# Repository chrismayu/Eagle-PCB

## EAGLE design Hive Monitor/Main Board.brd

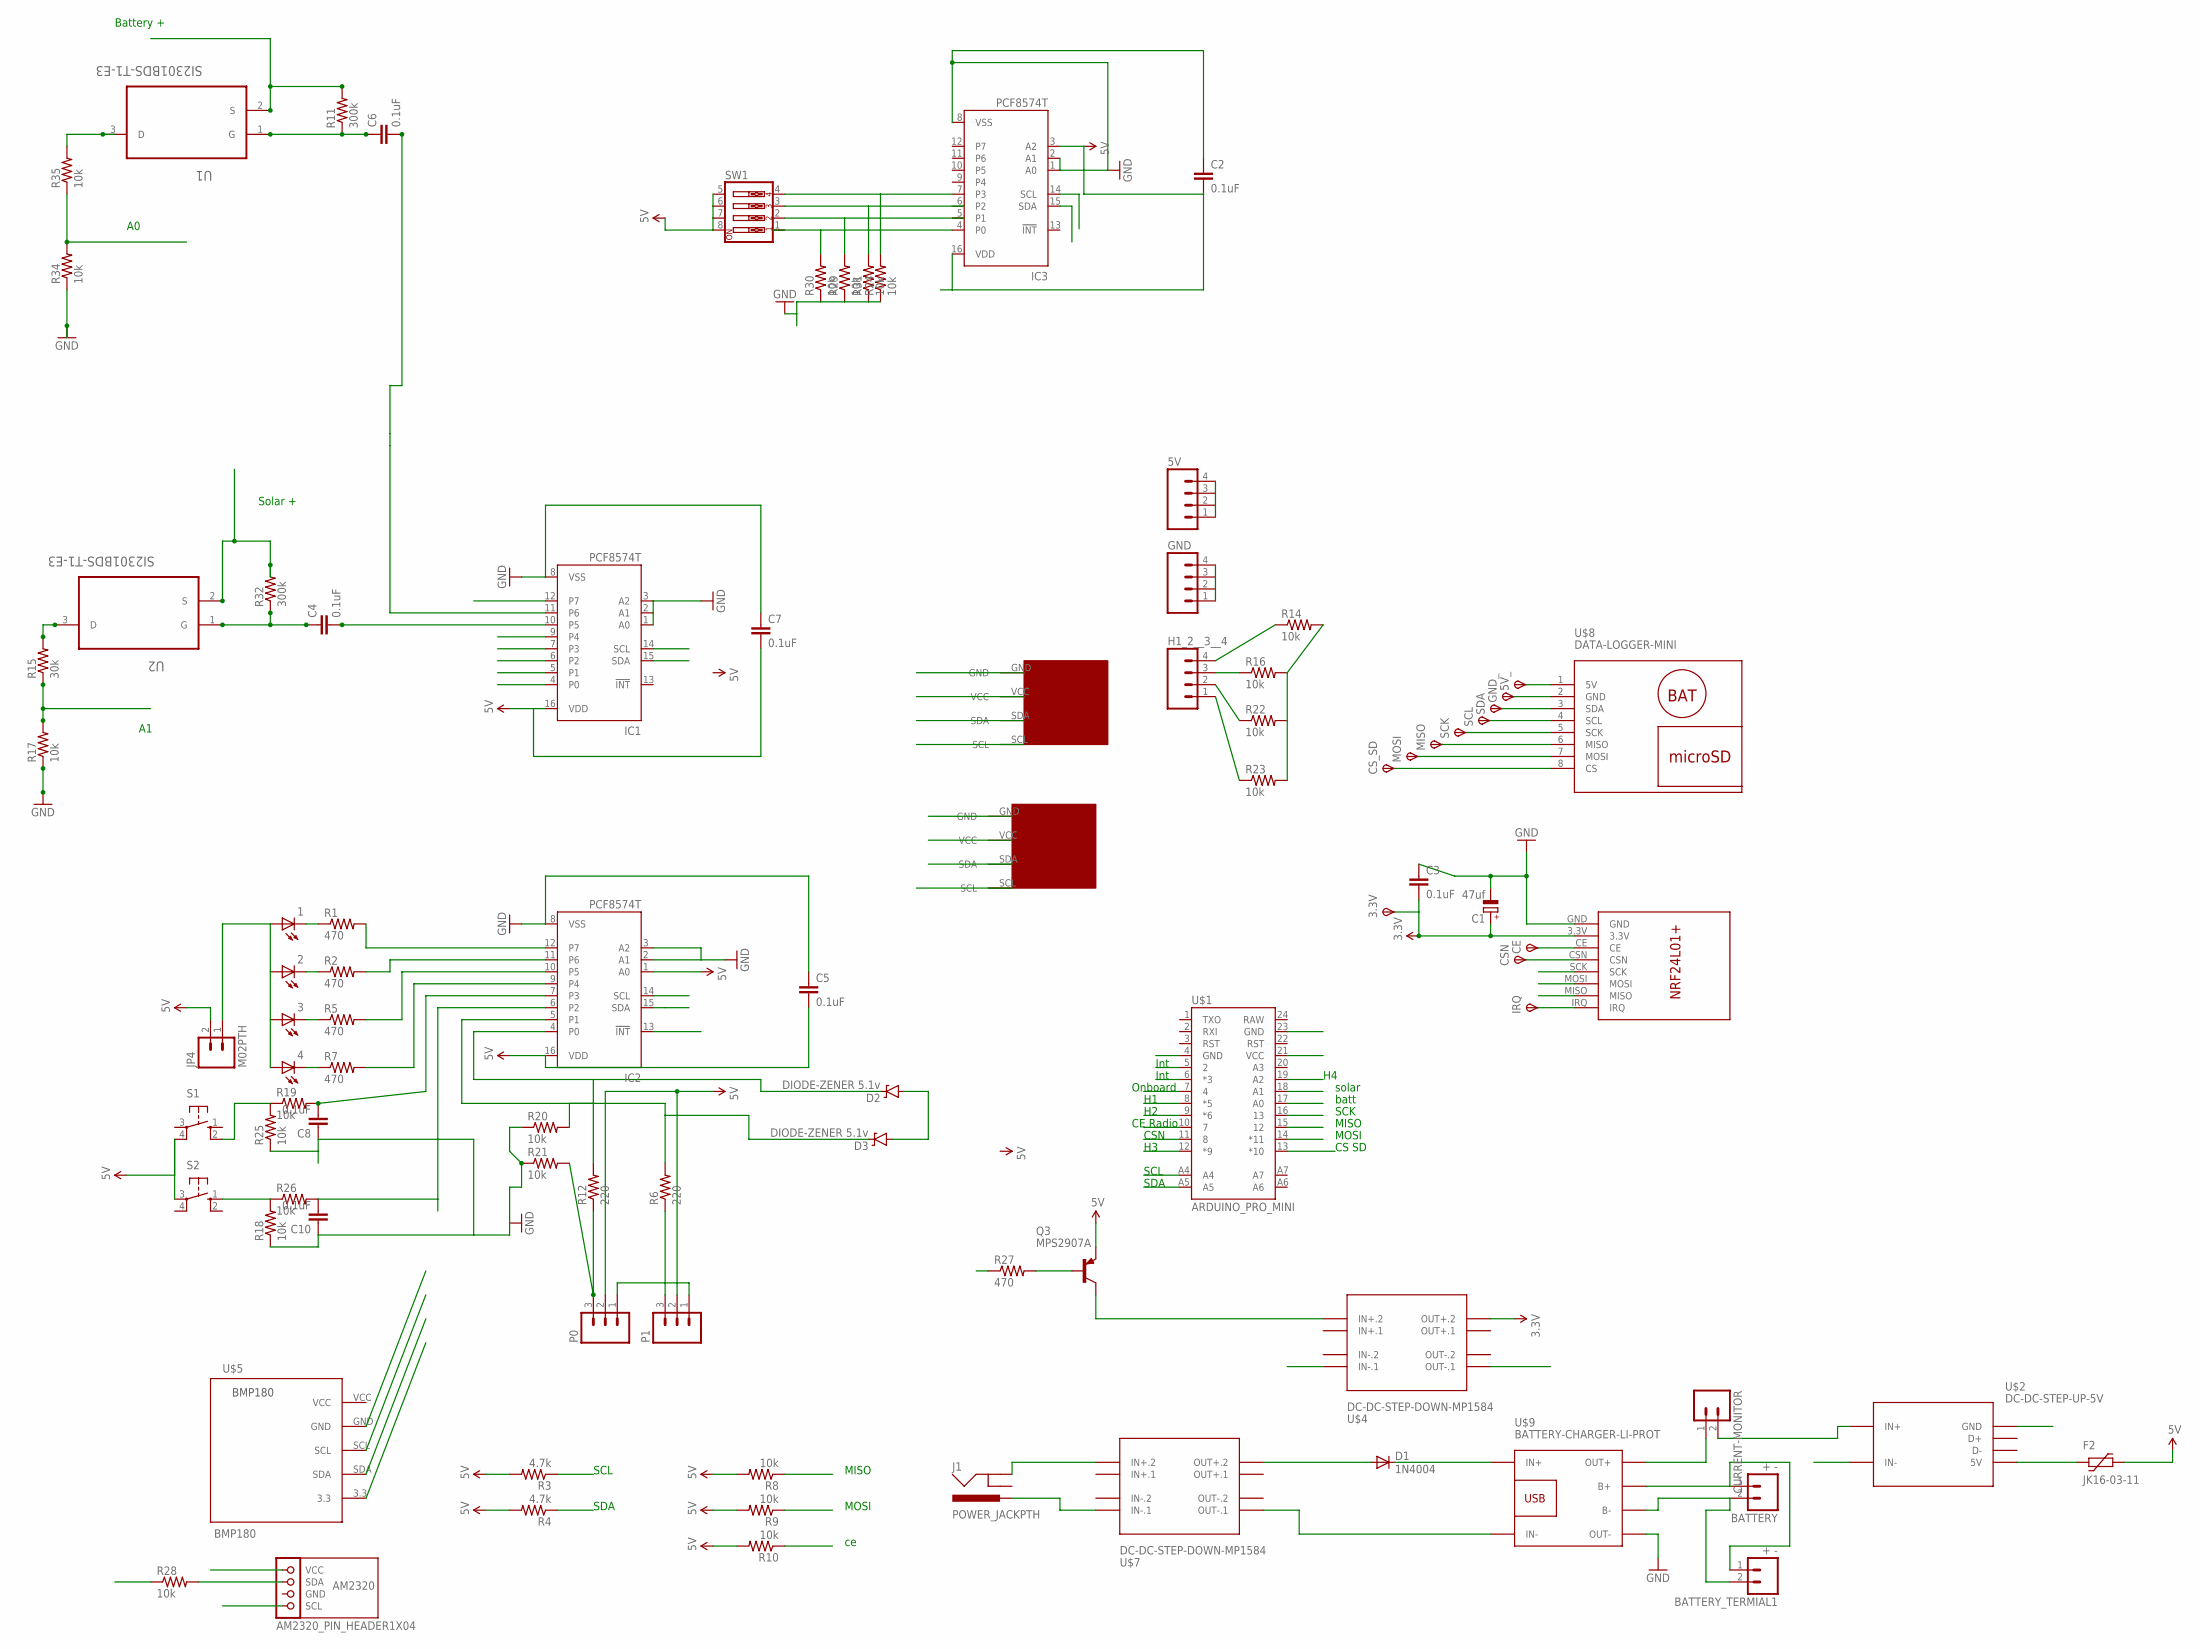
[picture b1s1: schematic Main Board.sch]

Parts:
1, 2, 3, 4: LED3MM
3.3V: TPSB1,27; B1,27
5V: M04PTH; 1X04
5V_: SCK; B1,27
AM2320: AM2320_PIN_HEADER1X04; 1X04
BATTERY: + -; 1X02
BATTERY_TERMIAL1: + -; 1X02
C1: 47uf; E2,5-5
C2, C3, C4, C5, C6, C7, C8, C10: 0.1uF; 0805
CE: TPSB1,27; B1,27
CSN: TPSB1,27; B1,27
CS_SD: TPSB1,27; B1,27
CURRENT-MONITOR: M02PTH; 1X02
D1: 1N4004; DO41-10
D2, D3: DIODE-ZENER 5.1v; DIODE-ZENER
F2: JK16-03-11
GND: M04PTH; 1X04
GND_: GND; B1,27
H1_2__3__4: M04PTH; 1X04
IC1, IC2, IC3: PCF8574T; SO16W
IRQ: TPSB1,27; B1,27
J1: POWER_JACKPTH; POWER_JACK_PTH
JP4: M02PTH; 1X02
MISO: TPSB1,27; B1,27
MOSI: TPSB1,27; B1,27
P0, P1: M03PTH; 1X03
Q3: MPS2907A; TO92-CBE
R1, R2, R5, R7, R27: 470; 1206
R3, R4: 4.7k; 1206
R6, R12: 220; 1206
R8, R9, R10, R14, R16, R18, R19, R20, R21, R22, R23, R24, R25, R26, R28, R29, R30, R31: 10k; 1206
R11, R32: 300k; 1/6W-RES
R15: 30k; 1/6W-RES
R17, R34, R35: 10k; 1/6W-RES
S1, S2: 10-XX; B3F-10XX
SCK: SCK; B1,27
SCL: SCK; B1,27
SDA: SCK; B1,27
SW1: SW_DIP-4; EDG-04
U1, U2: SI2301BDS-T1-E3; SOT95P237X112-3N
U$1: ARDUINO_PRO_MINI
U$2: DC-DC-STEP-UP-5V
U$3: NRF24L01
U$4, U$7: DC-DC-STEP-DOWN-MP1584
U$5: BMP180; 1X05
U$8: DATA-LOGGER-MINI
U$9: BATTERY-CHARGER-LI-PROT
U$10, U$11: TJC8-4P

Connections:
3.3V: 3.3V.TP, C1.+, C3.2, U$3.3.3V, U$4.OUT+.2, U$5.3.3
5V: 5V.1, 5V.2, 5V.3, 5V.4, 5V_.TP, AM2320.1 (VCC), C2.2, C5.2, C7.2, F2.P$2 (2), IC1.16 (VDD), IC2.1 (A0), IC2.16 (VDD), IC3.3 (A2), IC3.16 (VDD), JP4.2, P0.2, P1.2, Q3.E, R3.2, R4.2, R8.2, R9.2, R10.2, R14.2, R16.2, R22.2, R23.2, R28.1, S1.4 (P1), S2.3, SW1.5, SW1.6, SW1.7, SW1.8, U$1.21 (VCC), U$8.1 (5V), U$10.VCC, U$11.VCC
12B: IC1.12 (P7), R27.1
12B2: Q3.B, R27.2
A0: R34.2, R35.1, U$1.17 (A0)
A1: R15.1, R17.2, U$1.18 (A1)
B+: BATTERY.1, BATTERY_TERMIAL1.1, R11.2, U1.2 (S), U$9.B+
CE_RADIO: CE.TP, R10.1, U$1.10 (7), U$3.CE
CS-SD: CS_SD.TP, U$1.13 (*10), U$8.8 (CS)
CSN: U$1.11 (8)
GND: AM2320.4 (SCL), C1.-, C2.1, C3.1, C5.1, C7.1, C8.1, C10.1, D2.P$2 (A), D3.P$2 (A), GND.1, GND.2, GND.3, GND.4, GND_.TP, IC1.1 (A0), IC1.2 (A1), IC1.3 (A2), IC1.8 (VSS), IC2.2 (A1), IC2.3 (A2), IC2.8 (VSS), IC3.1 (A0), IC3.2 (A1), IC3.8 (VSS), P0.1, P1.1, R17.1, R18.1, R20.1, R21.1, R24.1, R25.1, R29.1, R30.1, R31.1, R34.1, U$1.4 (GND), U$1.23 (GND), U$2.GND, U$2.IN-, U$3.GND, U$4.IN-.1, U$4.OUT-.1, U$5.GND, U$8.2 (GND), U$9.OUT-, U$10.GND, U$11.GND
H1: H1_2__3__4.1, IC1.5 (P1), R23.1, U$1.8 (*5)
H2: H1_2__3__4.2, IC1.6 (P2), R22.1, U$1.9 (*6)
H3: H1_2__3__4.3, IC1.7 (P3), R16.1, U$1.12 (*9)
H4: H1_2__3__4.4, IC1.9 (P4), R14.1, U$1.19 (A2)
INT8574: IC2.13 (!INT), U$1.6 (*3)
IRQ: IRQ.TP, U$1.5 (2), U$3.IRQ
MISO: MISO.TP, R8.1, U$1.15 (12), U$3.MISO, U$8.6 (MISO)
MOSI: MOSI.TP, R9.1, U$1.14 (*11), U$3.MOSI, U$8.7 (MOSI)
unnamed: BATTERY.2, BATTERY_TERMIAL1.2, U$9.B-
unnamed: C6.2, IC1.11 (P6)
unnamed: 4.K (C), R7.1
unnamed: 3.K (C), R5.1
unnamed: 2.K (C), R2.1
unnamed: 1.K (C), R1.1
unnamed: IC2.12 (P7), R1.2
unnamed: 1.A, 2.A, 3.A, 4.A, JP4.1
unnamed: IC2.11 (P6), R2.2
unnamed: IC2.10 (P5), R5.2
unnamed: IC2.9 (P4), R7.2
unnamed: CURRENT-MONITOR.1, U$9.OUT+
unnamed: D2.P$1 (C), IC2.4 (P0), IC2.5 (P1), R12.2
unnamed: U$7.OUT-.1, U$9.IN-
unnamed: D1.C, U$9.IN+
unnamed: D1.A, U$7.OUT+.2
unnamed: F2.P$1 (1), U$2.5V
unnamed: CURRENT-MONITOR.2, U$2.IN+
unnamed: J1.PWR, U$7.IN-.1
unnamed: C8.2, IC2.7 (P3), R19.2
unnamed: C4.2, IC1.10 (P5)
unnamed: P0.3, R12.1, R21.2
unnamed: C10.2, IC2.6 (P2), R26.2
unnamed: P1.3, R6.1
unnamed: C4.1, R32.1, U2.1 (G)
unnamed: IC3.4 (P0), R30.2
unnamed: D3.P$1 (C), R6.2, R20.2
unnamed: R15.2, U2.3 (D)
unnamed: C6.1, R11.1, U1.1 (G)
unnamed: R19.1, R25.2, S1.2 (S1)
unnamed: Q3.C, U$4.IN+.2
unnamed: R29.2, SW1.2
unnamed: R31.2, SW1.3
unnamed: IC3.7 (P3), R24.2, SW1.4
unnamed: R35.2, U1.3 (D)
unnamed: CSN.TP, U$3.CSN
unnamed: R18.2, R26.1, S2.1 (S)
ONBOARD: AM2320.2 (SDA), IC1.4 (P0), R28.2, U$1.7 (4)
S+: J1.GND, R32.2, U2.2 (S), U$7.IN+.2
SCK: SCK.TP, U$1.16 (13), U$3.SCK, U$8.5 (SCK)
SCL: IC1.14 (SCL), IC2.14 (SCL), IC3.14 (SCL), R3.1, SCL.TP, U$1.A5, U$5.SCL, U$8.4 (SCL), U$10.SCL, U$11.SCL
SDA: IC1.15 (SDA), IC2.15 (SDA), IC3.15 (SDA), R4.1, SDA.TP, U$1.A4, U$5.SDA, U$8.3 (SDA), U$10.SDA, U$11.SDA

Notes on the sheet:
MOSI
MISO
SCL
SDA
Solar +
Battery +
Int
CE Radio
CSN
solar
batt
SCK
Onboard
CS SD

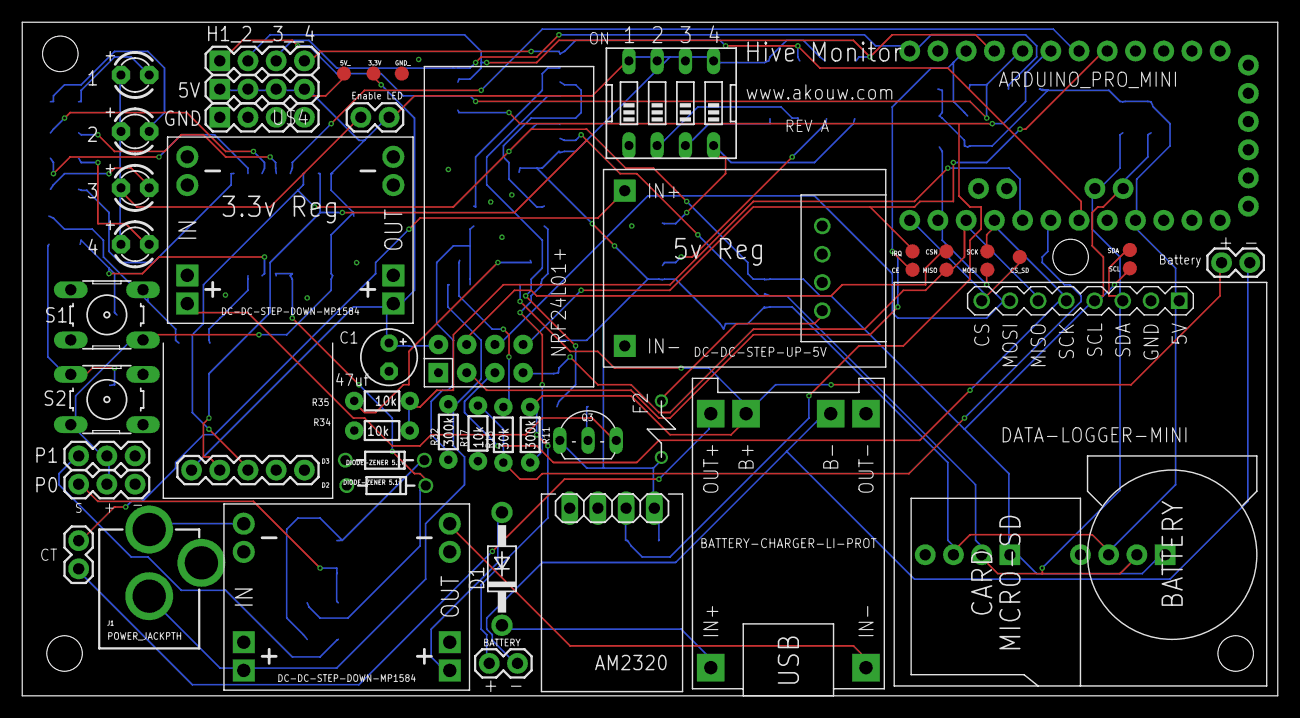
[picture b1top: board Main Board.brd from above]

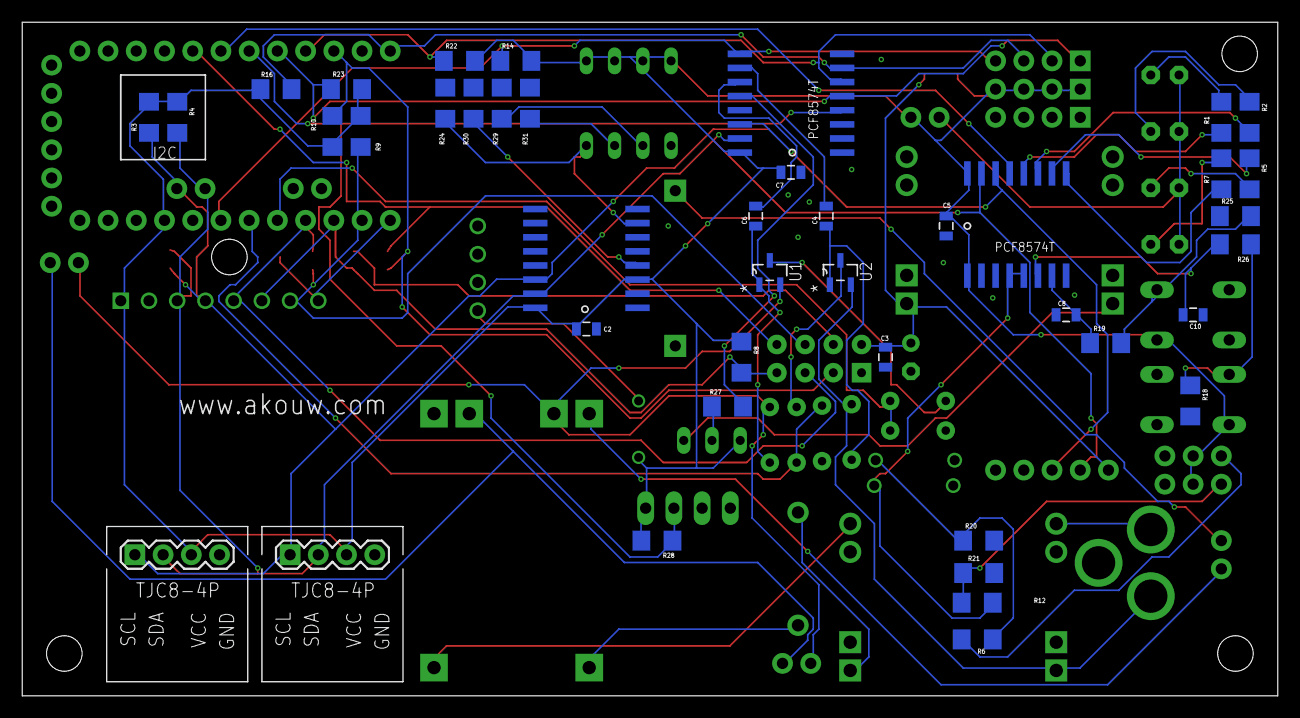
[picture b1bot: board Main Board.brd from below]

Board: 2 copper layers, 113.0 x 60.6 mm, 92 parts (42 on the bottom side), 60 nets.

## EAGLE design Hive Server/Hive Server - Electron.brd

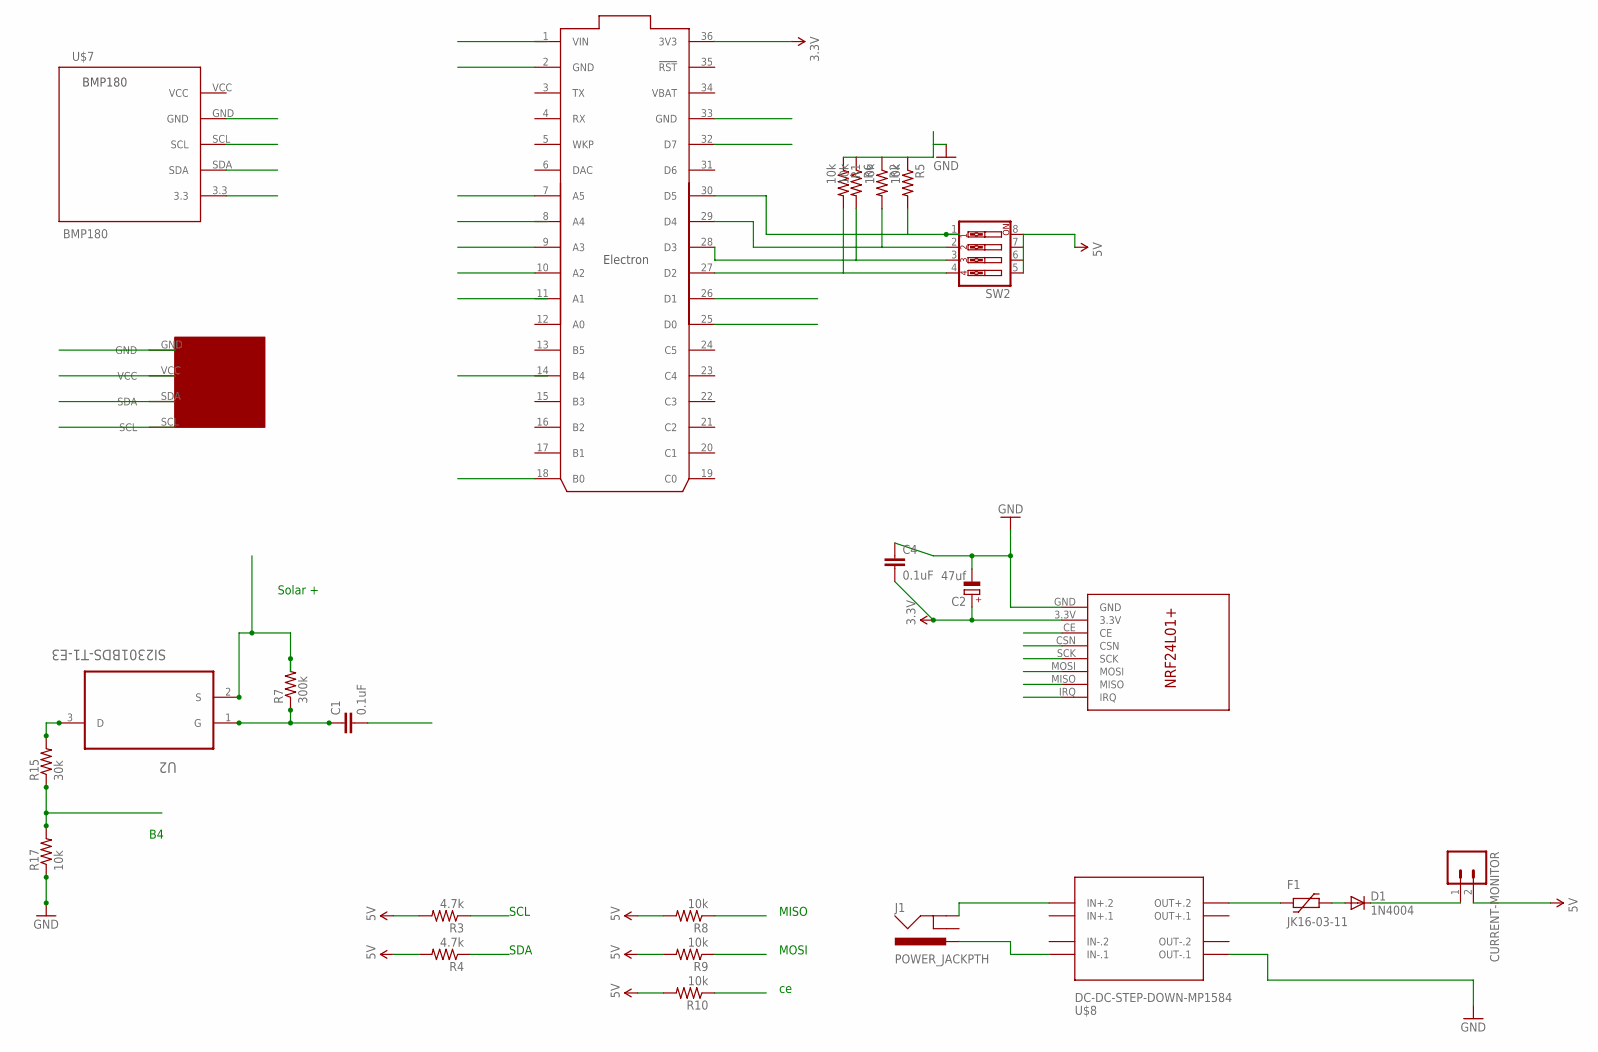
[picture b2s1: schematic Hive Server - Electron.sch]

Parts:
C1, C4: 0.1uF; 0805
C2: 47uf; E2,5-5
CURRENT-MONITOR: M02PTH; 1X02
D1: 1N4004; DO41-10
F1: JK16-03-11
J1: POWER_JACKPTH; POWER_JACK_PTH
R1, R2, R5, R6, R8, R9, R10: 10k; 1206
R3, R4: 4.7k; 1206
R7: 300k; 1/6W-RES
R15: 30k; 1/6W-RES
R17: 10k; 1/6W-RES
SW2: SW_DIP-4; EDG-04
U2: SI2301BDS-T1-E3; SOT95P237X112-3N
U$1: ELECTRON_WITH_HEADERS; ELECTRON
U$6: NRF24L01
U$7: BMP180; 1X05
U$8: DC-DC-STEP-DOWN-MP1584
U$13: TJC8-4P

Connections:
3.3V: C2.+, C4.2, U$1.36 (3V3), U$6.3.3V, U$7.3.3
5V: CURRENT-MONITOR.2, R3.2, R4.2, R8.2, R9.2, R10.2, SW2.5, SW2.6, SW2.7, SW2.8, U$13.VCC
B4: R15.1, R17.2
CE_RADIO: R10.1, U$6.CE
CSN: U$1.10 (A2), U$6.CSN
D7: C1.2, U$1.32 (D7)
GND: C2.-, C4.1, R1.1, R2.1, R5.1, R6.1, R17.1, U$1.2 (GND), U$1.33 (GND), U$6.GND, U$7.GND, U$8.OUT-.1, U$13.GND
IRQ: U$1.18 (B0), U$6.IRQ
MISO: R8.1, U$6.MISO
MOSI: R9.1, U$1.7 (A5), U$6.MOSI
unnamed: CURRENT-MONITOR.1, D1.C
unnamed: R5.2, SW2.1, U$1.30 (D5)
unnamed: R2.2, SW2.2, U$1.29 (D4)
unnamed: R6.2, SW2.3, U$1.28 (D3)
unnamed: R1.2, SW2.4, U$1.27 (D2)
unnamed: D1.A, F1.P$2 (2)
unnamed: F1.P$1 (1), U$8.OUT+.2
unnamed: J1.PWR, U$8.IN-.1
unnamed: C1.1, R7.1, U2.1 (G)
unnamed: R15.2, U2.3 (D)
S+: J1.GND, R7.2, U2.2 (S), U$8.IN+.2
SCK: U$1.9 (A3), U$6.SCK
SCL: R3.1, U$1.26 (D1), U$7.SCL, U$13.SCL
SDA: R4.1, U$1.25 (D0), U$7.SDA, U$13.SDA
VBAT: U$1.34 (VBAT)
VIN: U$1.1 (VIN)

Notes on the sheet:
MOSI
MISO
SCL
SDA
Solar +

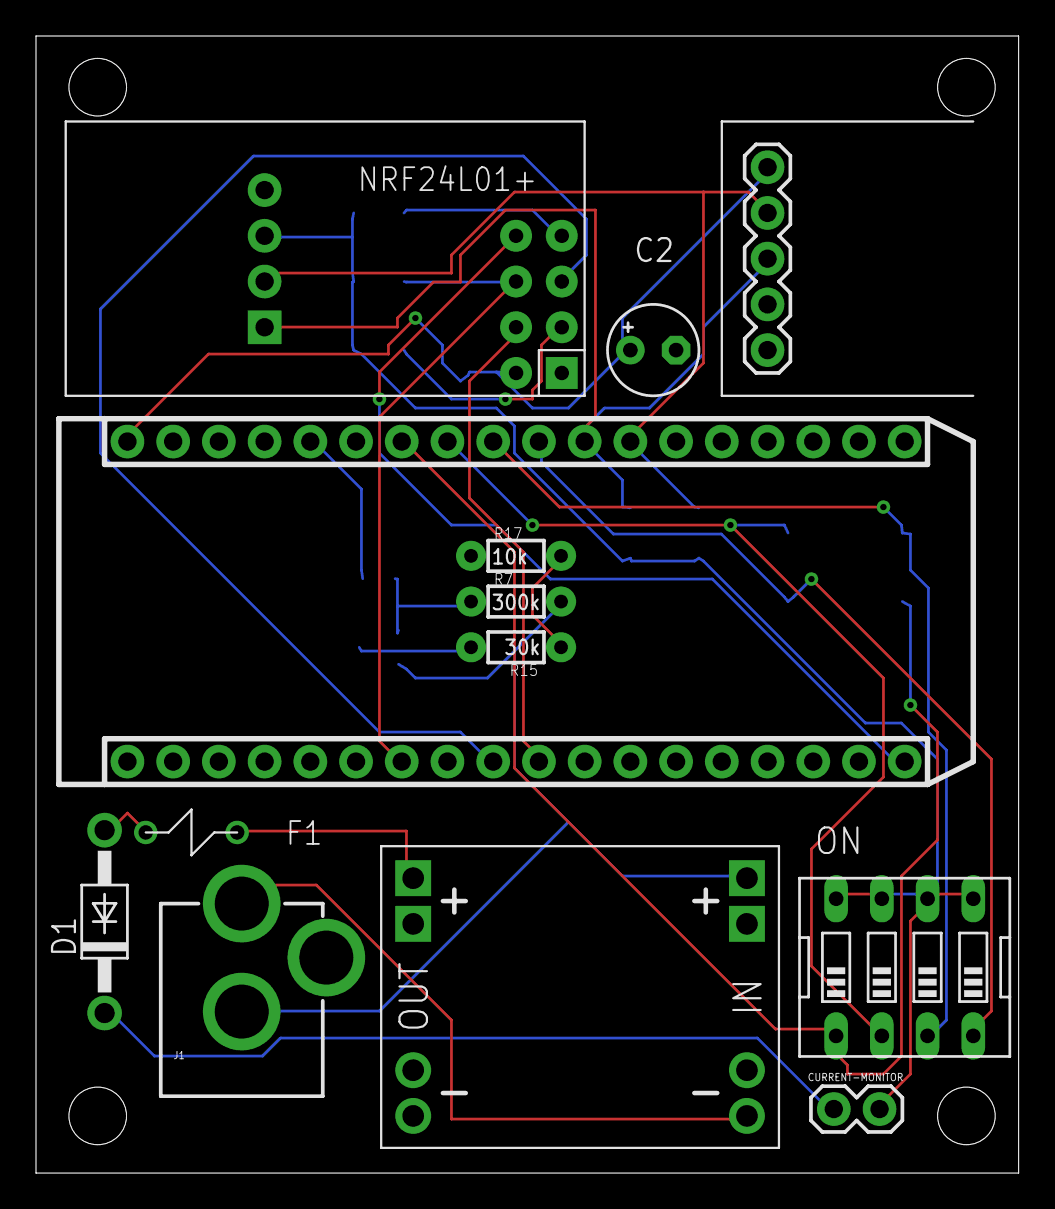
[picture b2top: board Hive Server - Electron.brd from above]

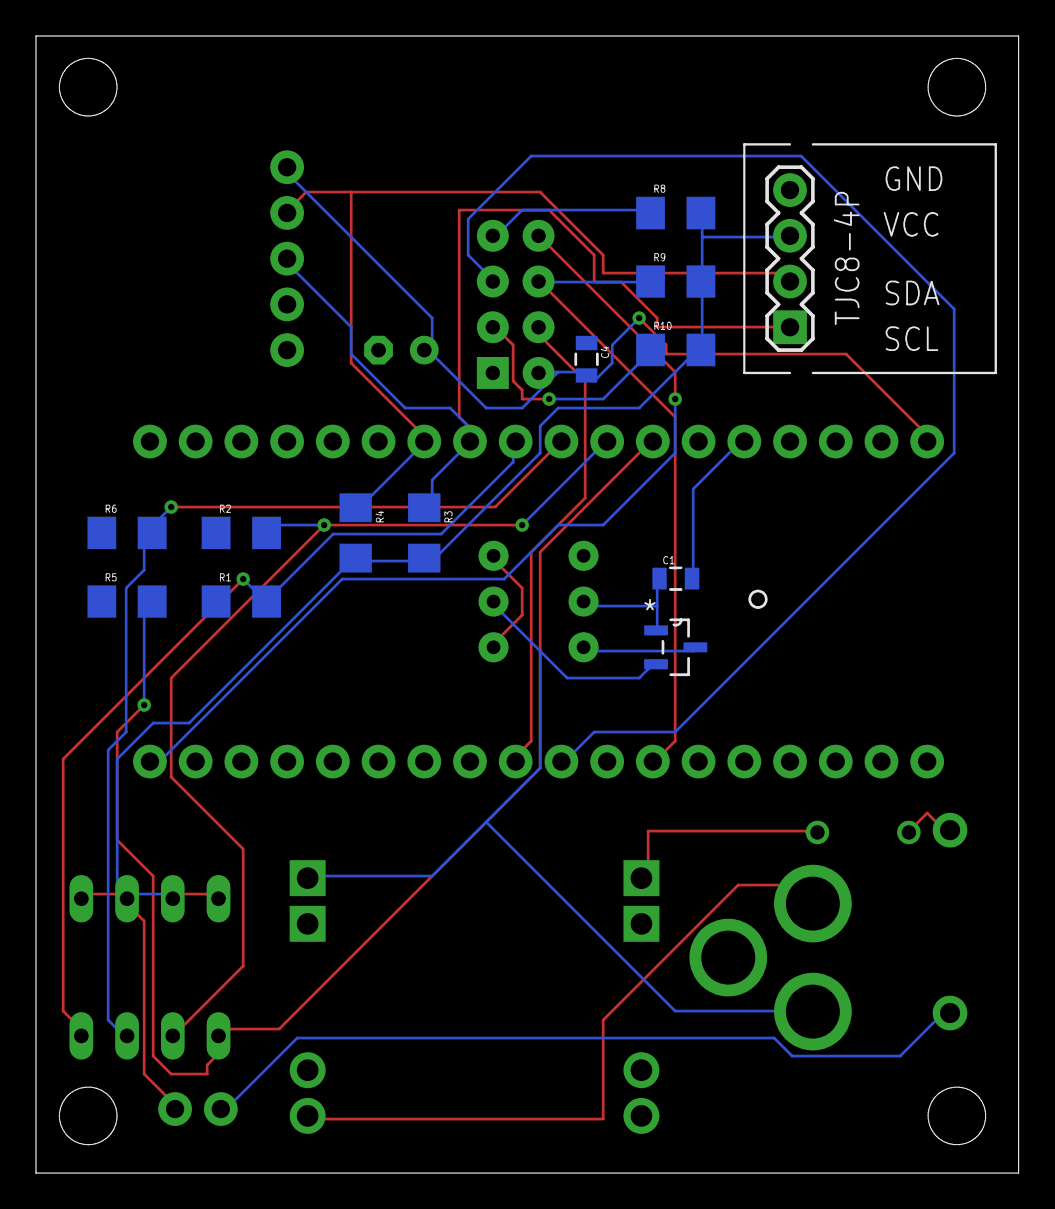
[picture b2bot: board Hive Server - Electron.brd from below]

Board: 2 copper layers, 54.6 x 63.2 mm, 26 parts (13 on the bottom side), 24 nets.

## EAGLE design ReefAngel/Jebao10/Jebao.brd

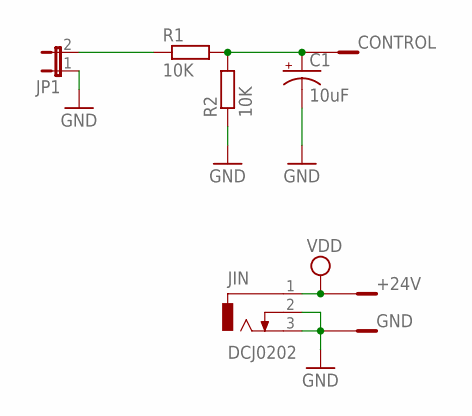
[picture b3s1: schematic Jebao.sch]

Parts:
+24V: POWERPIN
C1: 10uF; A/3216-18R
CONTROL: POWERPIN
GND: POWERPIN
JIN: DCJ0202
JP1: JP1E; JP1
R1, R2: 10K; R0805

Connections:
12V: +24V.1, JIN.1
GND: C1.-, GND.1, JIN.2, JIN.3, JP1.1, R2.1
unnamed: JP1.2, R1.1
unnamed: C1.+, CONTROL.1, R1.2, R2.2

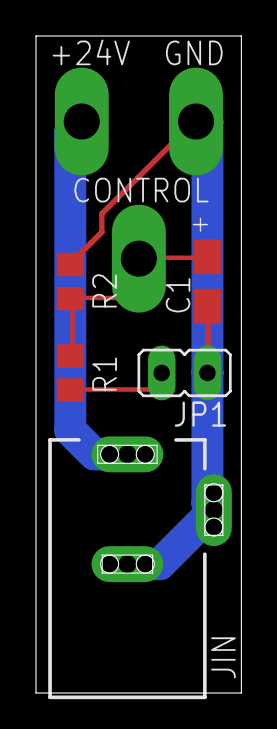
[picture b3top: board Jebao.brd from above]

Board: 2 copper layers, 11.4 x 36.5 mm, 8 parts (0 on the bottom side), 4 nets.

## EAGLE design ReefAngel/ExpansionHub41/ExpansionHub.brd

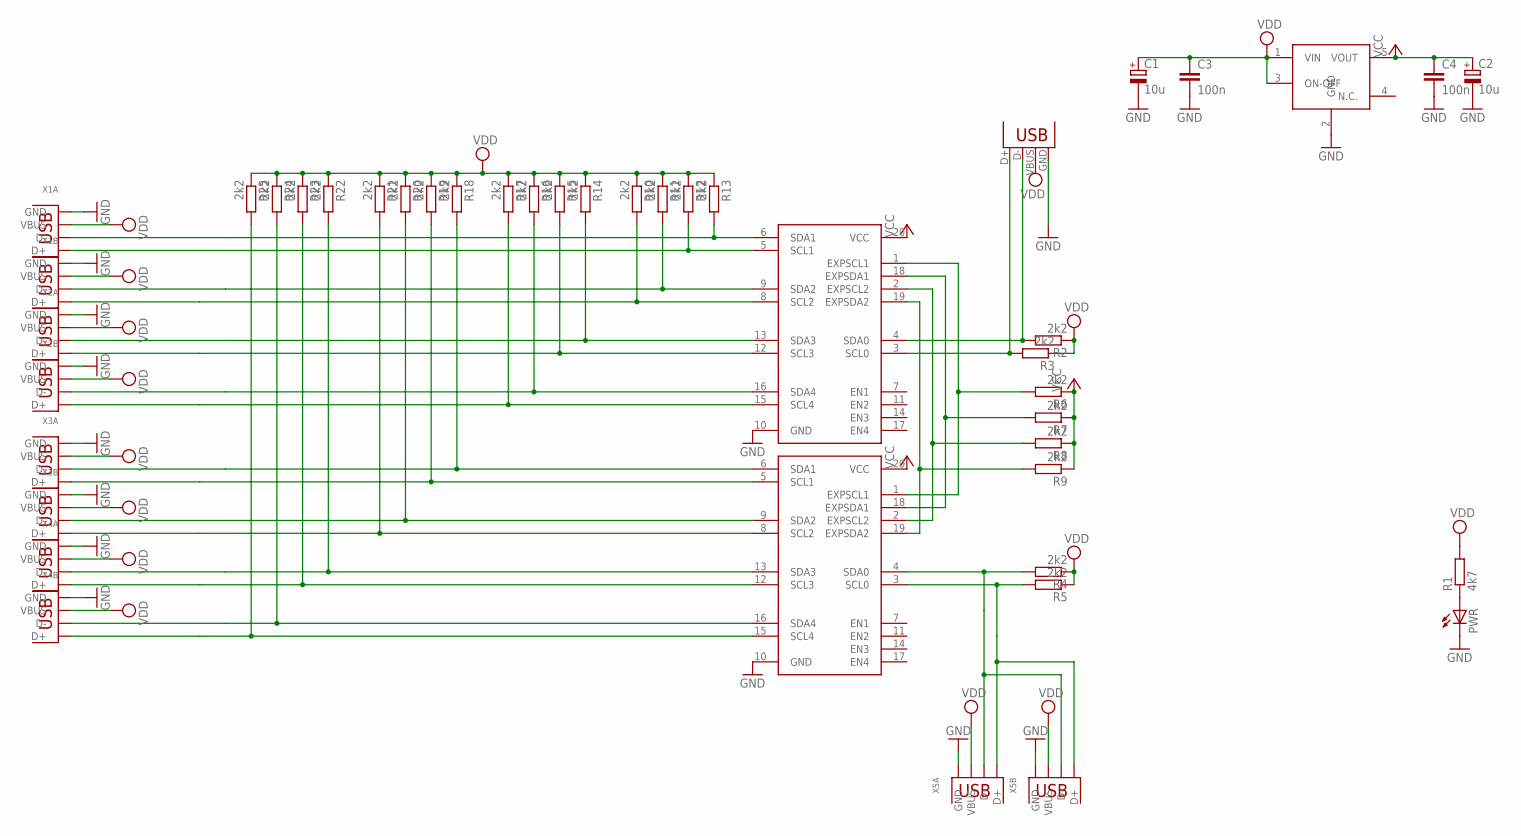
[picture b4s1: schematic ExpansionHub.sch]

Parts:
C1, C2: 10u; A/3216-18W
C3, C4: 100n; C0805
IC1, IC2: PCA9518; TSSOP20
PWR: LED3MM
R1: 4k7; R0805W
R2, R3, R4, R5, R6, R7, R8, R9, R10, R11, R12, R13, R14, R15, R16, R17, R18, R19, R20, R21, R22, R23, R24, R25: 2k2; R0805
U1: LP2985; SOT23-5
X1, X2, X3, X4, X5: DUA-USB; DUAL
X11: USBSMD; USB-MINIB

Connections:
GND: C1.-, C2.-, C3.2, C4.2, IC1.10 (GND), IC2.10 (GND), PWR.K (C), U1.2 (GND), X1.1-4 (GND), X1.2-4 (GND), X2.1-4 (GND), X2.2-4 (GND), X3.1-4 (GND), X3.2-4 (GND), X4.1-4 (GND), X4.2-4 (GND), X5.1-4 (GND), X5.2-4 (GND), X11.GND
unnamed: IC1.19 (EXPSDA2), IC2.19 (EXPSDA2), R9.2
unnamed: IC1.2 (EXPSCL2), IC2.2 (EXPSCL2), R8.2
unnamed: IC1.18 (EXPSDA1), IC2.18 (EXPSDA1), R7.2
unnamed: IC1.4 (SDA0), R2.2, X11.D-
unnamed: IC1.3 (SCL0), R3.2, X11.D+
unnamed: IC1.1 (EXPSCL1), IC2.1 (EXPSCL1), R6.2
unnamed: IC2.3 (SCL0), R5.2, X5.1-3 (D+), X5.2-3 (D+)
unnamed: IC2.4 (SDA0), R4.2, X5.1-2 (D-), X5.2-2 (D-)
unnamed: IC1.9 (SDA2), R11.2, X1.2-2 (D-)
unnamed: PWR.A, R1.1
unnamed: IC2.15 (SCL4), R25.2, X4.2-3 (D+)
unnamed: IC1.8 (SCL2), R10.2, X1.2-3 (D+)
unnamed: IC2.16 (SDA4), R24.2, X4.2-2 (D-)
unnamed: IC1.12 (SCL3), R15.2, X2.1-3 (D+)
unnamed: IC1.15 (SCL4), R17.2, X2.2-3 (D+)
unnamed: IC2.5 (SCL1), R19.2, X3.1-3 (D+)
unnamed: IC2.8 (SCL2), R21.2, X3.2-3 (D+)
unnamed: IC2.12 (SCL3), R23.2, X4.1-3 (D+)
unnamed: IC1.6 (SDA1), R13.2, X1.1-2 (D-)
unnamed: IC1.13 (SDA3), R14.2, X2.1-2 (D-)
unnamed: IC1.16 (SDA4), R16.2, X2.2-2 (D-)
unnamed: IC2.6 (SDA1), R18.2, X3.1-2 (D-)
unnamed: IC2.9 (SDA2), R20.2, X3.2-2 (D-)
unnamed: IC2.13 (SDA3), R22.2, X4.1-2 (D-)
unnamed: IC1.5 (SCL1), R12.2, X1.1-3 (D+)
VCC: C2.+, C4.1, IC1.20 (VCC), IC2.20 (VCC), R6.1, R7.1, R8.1, R9.1, U1.5 (VOUT)
VDD: C1.+, C3.1, R1.2, R2.1, R3.1, R4.1, R5.1, R10.1, R11.1, R12.1, R13.1, R14.1, R15.1, R16.1, R17.1, R18.1, R19.1, R20.1, R21.1, R22.1, R23.1, R24.1, R25.1, U1.1 (VIN), U1.3 (ON-OFF), X1.1-1 (VBUS), X1.2-1 (VBUS), X2.1-1 (VBUS), X2.2-1 (VBUS), X3.1-1 (VBUS), X3.2-1 (VBUS), X4.1-1 (VBUS), X4.2-1 (VBUS), X5.1-1 (VBUS), X5.2-1 (VBUS), X11.VBUS

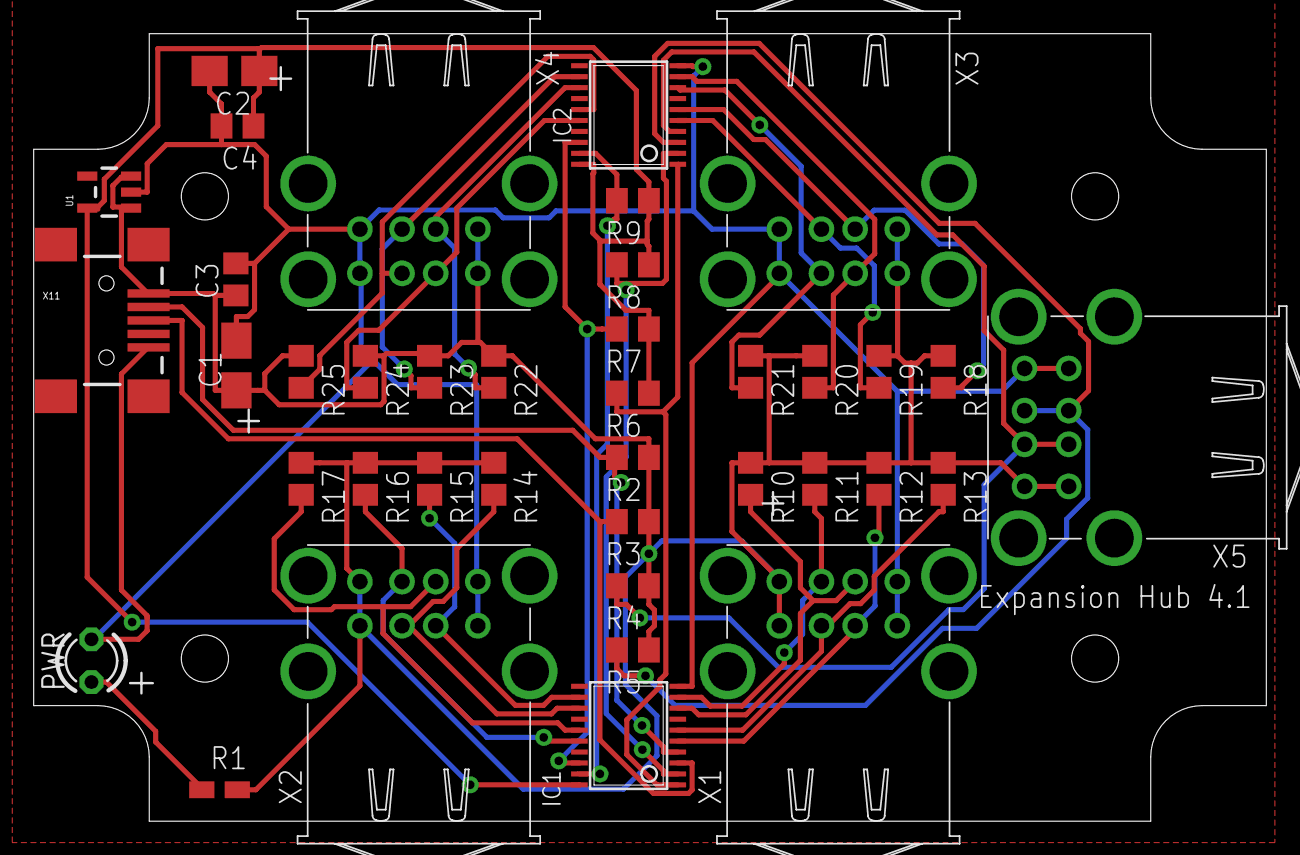
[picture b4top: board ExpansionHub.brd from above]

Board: 2 copper layers, 73.2 x 46.7 mm, 39 parts (0 on the bottom side), 28 nets.

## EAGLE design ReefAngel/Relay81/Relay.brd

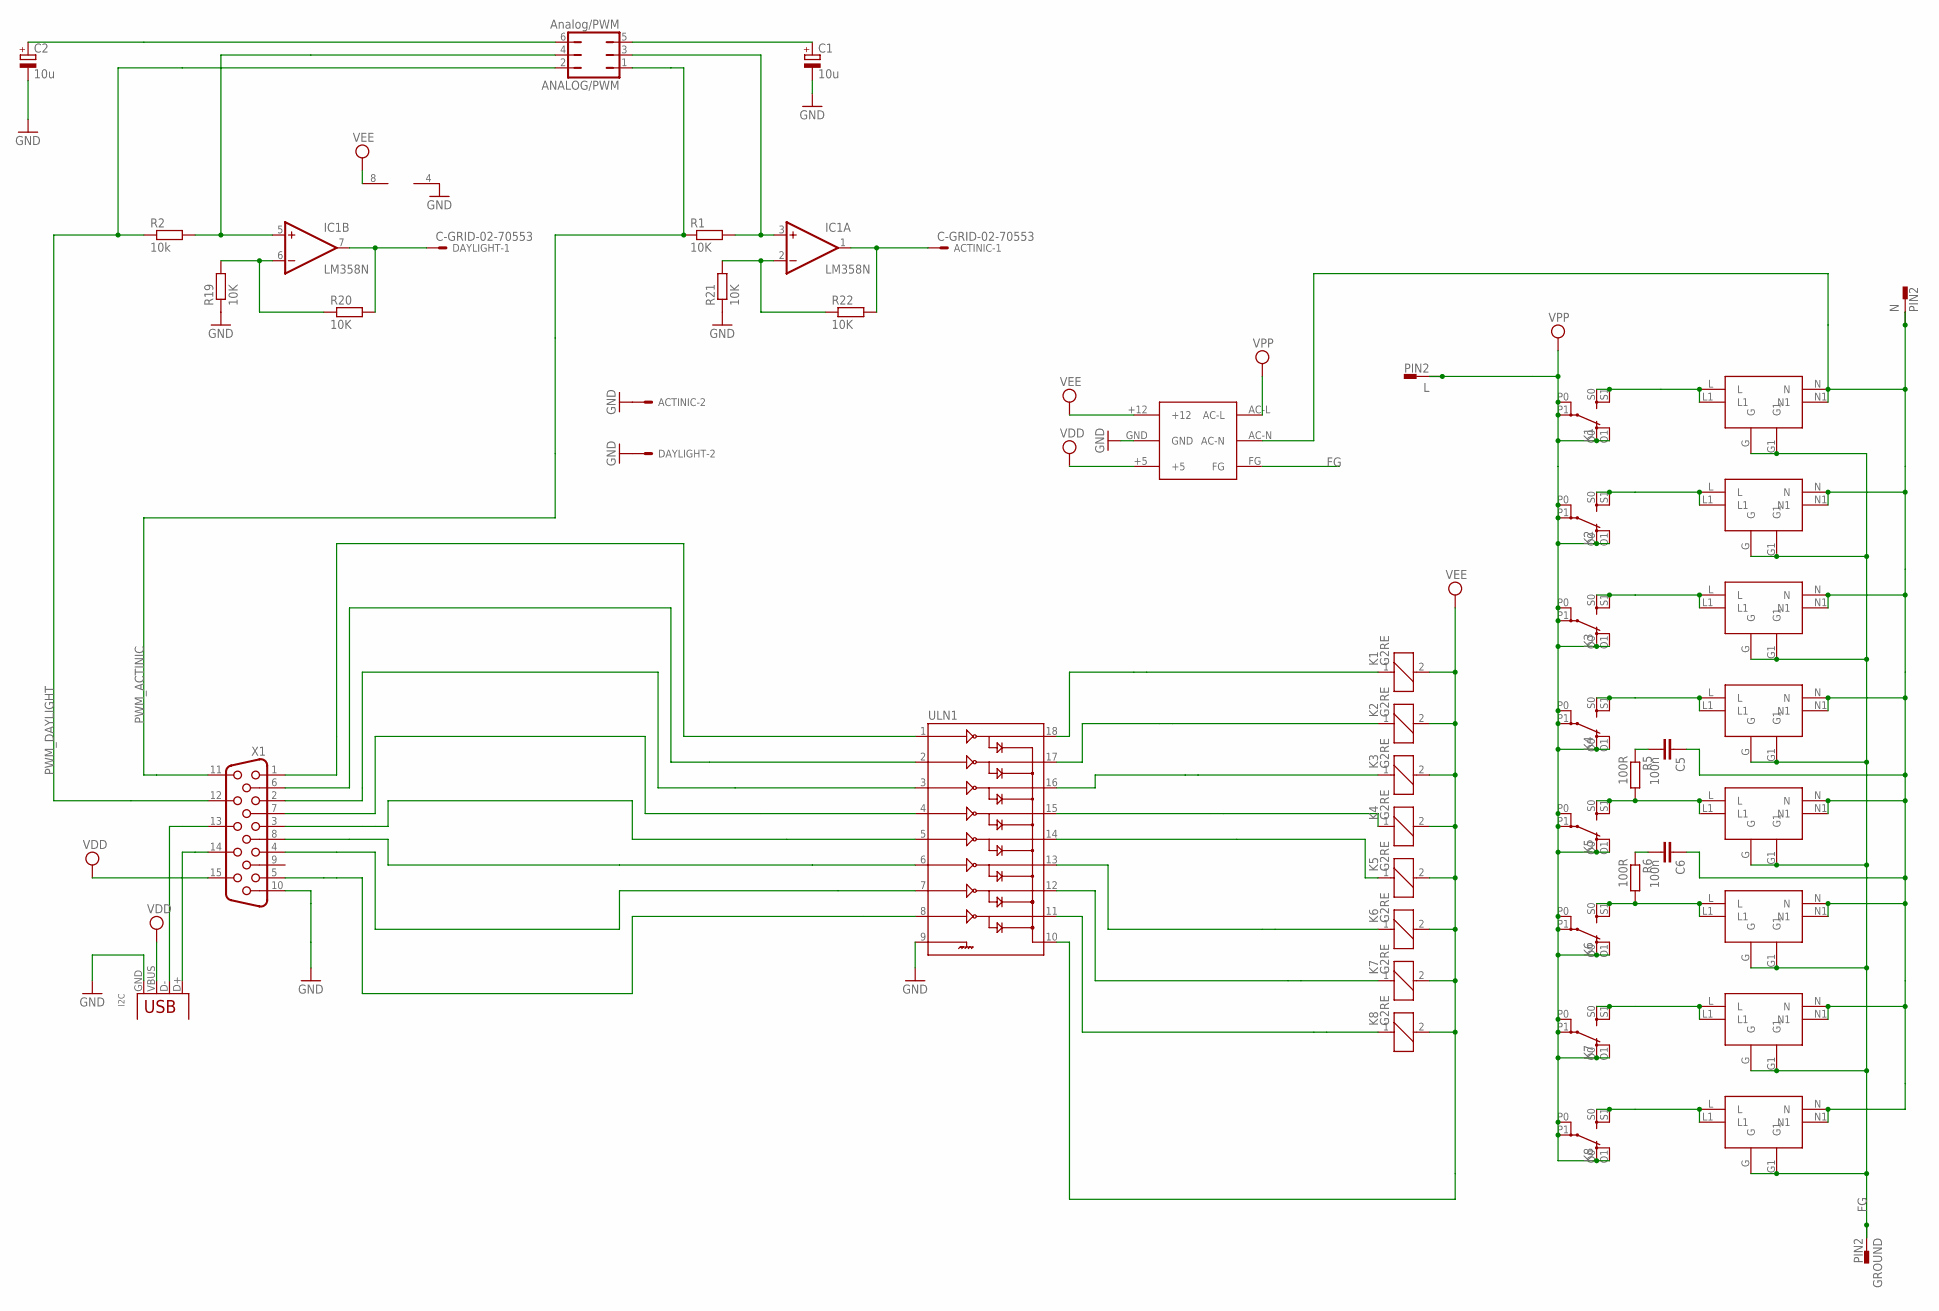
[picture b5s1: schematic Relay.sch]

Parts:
ACTINIC: C-GRID-02-70553; 70553-02
ANALOG/PWM: Analog/PWM; JP3Q
C1, C2: 10u; E2-5
C5, C6: 100n; C075-032X103
DAYLIGHT: C-GRID-02-70553; 70553-02
GROUND: PIN2; F061.100-INLET
I2C: USB-A-H
IC1: LM358N; DIL08
K1, K2, K3, K4, K5, K6, K7, K8: G2RE
L: PIN2; F061.100-INLET
N: PIN2; F061.100-INLET
O1, O2, O3, O4, O5, O6, O7, O8: SOCKET1; SOCKET
PS1: AC2200512DC
R1, R19, R20, R21, R22: 10K; 0207/7
R2: 10k; 0207/7
R5, R6: 100R; 0411/12
ULN1: ULN2803DIP; DIL18
X1: HF15H; HDF15H

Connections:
FG: GROUND.A1 (1), GROUND.A2 (1.1), O1.G, O1.G1, O2.G, O2.G1, O3.G, O3.G1, O4.G, O4.G1, O5.G, O5.G1, O6.G, O6.G1, O7.G, O7.G1, O8.G, O8.G1, PS1.FG
GND: ACTINIC.2, C1.-, C2.-, DAYLIGHT.2, I2C.GND, IC1.4 (V-), PS1.GND, R19.1, R21.1, ULN1.9, X1.10
unnamed: K1.S0 (S), K1.S1 (S), O1.L, O1.L1
unnamed: ULN1.2, X1.6
unnamed: K2.S0 (S), K2.S1 (S), O2.L, O2.L1
unnamed: ULN1.4, X1.7
unnamed: ULN1.5, X1.3
unnamed: K3.S0 (S), K3.S1 (S), O3.L, O3.L1
unnamed: ULN1.7, X1.4
unnamed: K4.S0 (S), K4.S1 (S), O4.L, O4.L1
unnamed: ANALOG/PWM.5, C1.+
unnamed: ULN1.1, X1.1
unnamed: K5.S0 (S), K5.S1 (S), O5.L, O5.L1, R5.2
unnamed: ULN1.3, X1.2
unnamed: K6.S0 (S), K6.S1 (S), O6.L, O6.L1, R6.2
unnamed: I2C.D-, X1.13
unnamed: K7.S0 (S), K7.S1 (S), O7.L, O7.L1
unnamed: ULN1.8, X1.5
unnamed: K1.1, ULN1.18
unnamed: K2.1, ULN1.17
unnamed: K8.S0 (S), K8.S1 (S), O8.L, O8.L1
unnamed: K3.1, ULN1.16
unnamed: K4.1, ULN1.15
unnamed: ANALOG/PWM.6, C2.+
unnamed: K6.1, ULN1.13
unnamed: K7.1, ULN1.12
unnamed: K8.1, ULN1.11
unnamed: ANALOG/PWM.3, IC1.3 (+IN), R1.2
unnamed: ANALOG/PWM.4, IC1.5 (+IN), R2.2
unnamed: DAYLIGHT.1, IC1.7 (OUT), R20.2
unnamed: ACTINIC.1, IC1.1 (OUT), R22.2
unnamed: C5.2, R5.1
unnamed: C6.2, R6.1
unnamed: C5.1, C6.1, N.A1 (1), N.A2 (1.1), O1.N, O1.N1, O2.N, O2.N1, O3.N, O3.N1, O4.N, O4.N1, O5.N, O5.N1, O6.N, O6.N1, O7.N, O7.N1, O8.N, O8.N1, PS1.AC-N
unnamed: ULN1.6, X1.8
unnamed: I2C.D+, X1.14
unnamed: K5.1, ULN1.14
unnamed: IC1.6 (-IN), R19.2, R20.1
unnamed: IC1.2 (-IN), R21.2, R22.1
PWM_ACTINIC: ANALOG/PWM.1, R1.1, X1.11
PWM_DAYLIGHT: ANALOG/PWM.2, R2.1, X1.12
VDD: I2C.VBUS, PS1.+5, X1.15
VEE: IC1.8 (V+), K1.2, K2.2, K3.2, K4.2, K5.2, K6.2, K7.2, K8.2, PS1.+12, ULN1.10
VPP: K1.O0 (O), K1.O1 (O), K1.P0, K1.P1, K2.O0 (O), K2.O1 (O), K2.P0, K2.P1, K3.O0 (O), K3.O1 (O), K3.P0, K3.P1, K4.O0 (O), K4.O1 (O), K4.P0, K4.P1, K5.O0 (O), K5.O1 (O), K5.P0, K5.P1, K6.O0 (O), K6.O1 (O), K6.P0, K6.P1, K7.O0 (O), K7.O1 (O), K7.P0, K7.P1, K8.O0 (O), K8.O1 (O), K8.P0, K8.P1, L.A1 (1), L.A2 (1.1), PS1.AC-L

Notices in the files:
parts and their libraries:
SparkFun-Boards: Licensing: Creative Commons ShareAlike 4.0 International - https://creativecommons.org/licenses/by-sa/4.0
diy-modules: Released under the Creative Commons Attribution 4.0 International License: http://creativecommons.org/licenses/by/4.0
